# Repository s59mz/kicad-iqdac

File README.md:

# iqdac
AD9957 DAC test module for the Z-Turn I/O expansion card

Schematic:
[iqdac.pdf](iqdac.pdf)

BOM:
[iqdac.csv](iqdac.csv)

Gerbers:
[gerbers.zip](https://github.com/s59mz/kicad-iqdac/raw/main/gerbers.zip)

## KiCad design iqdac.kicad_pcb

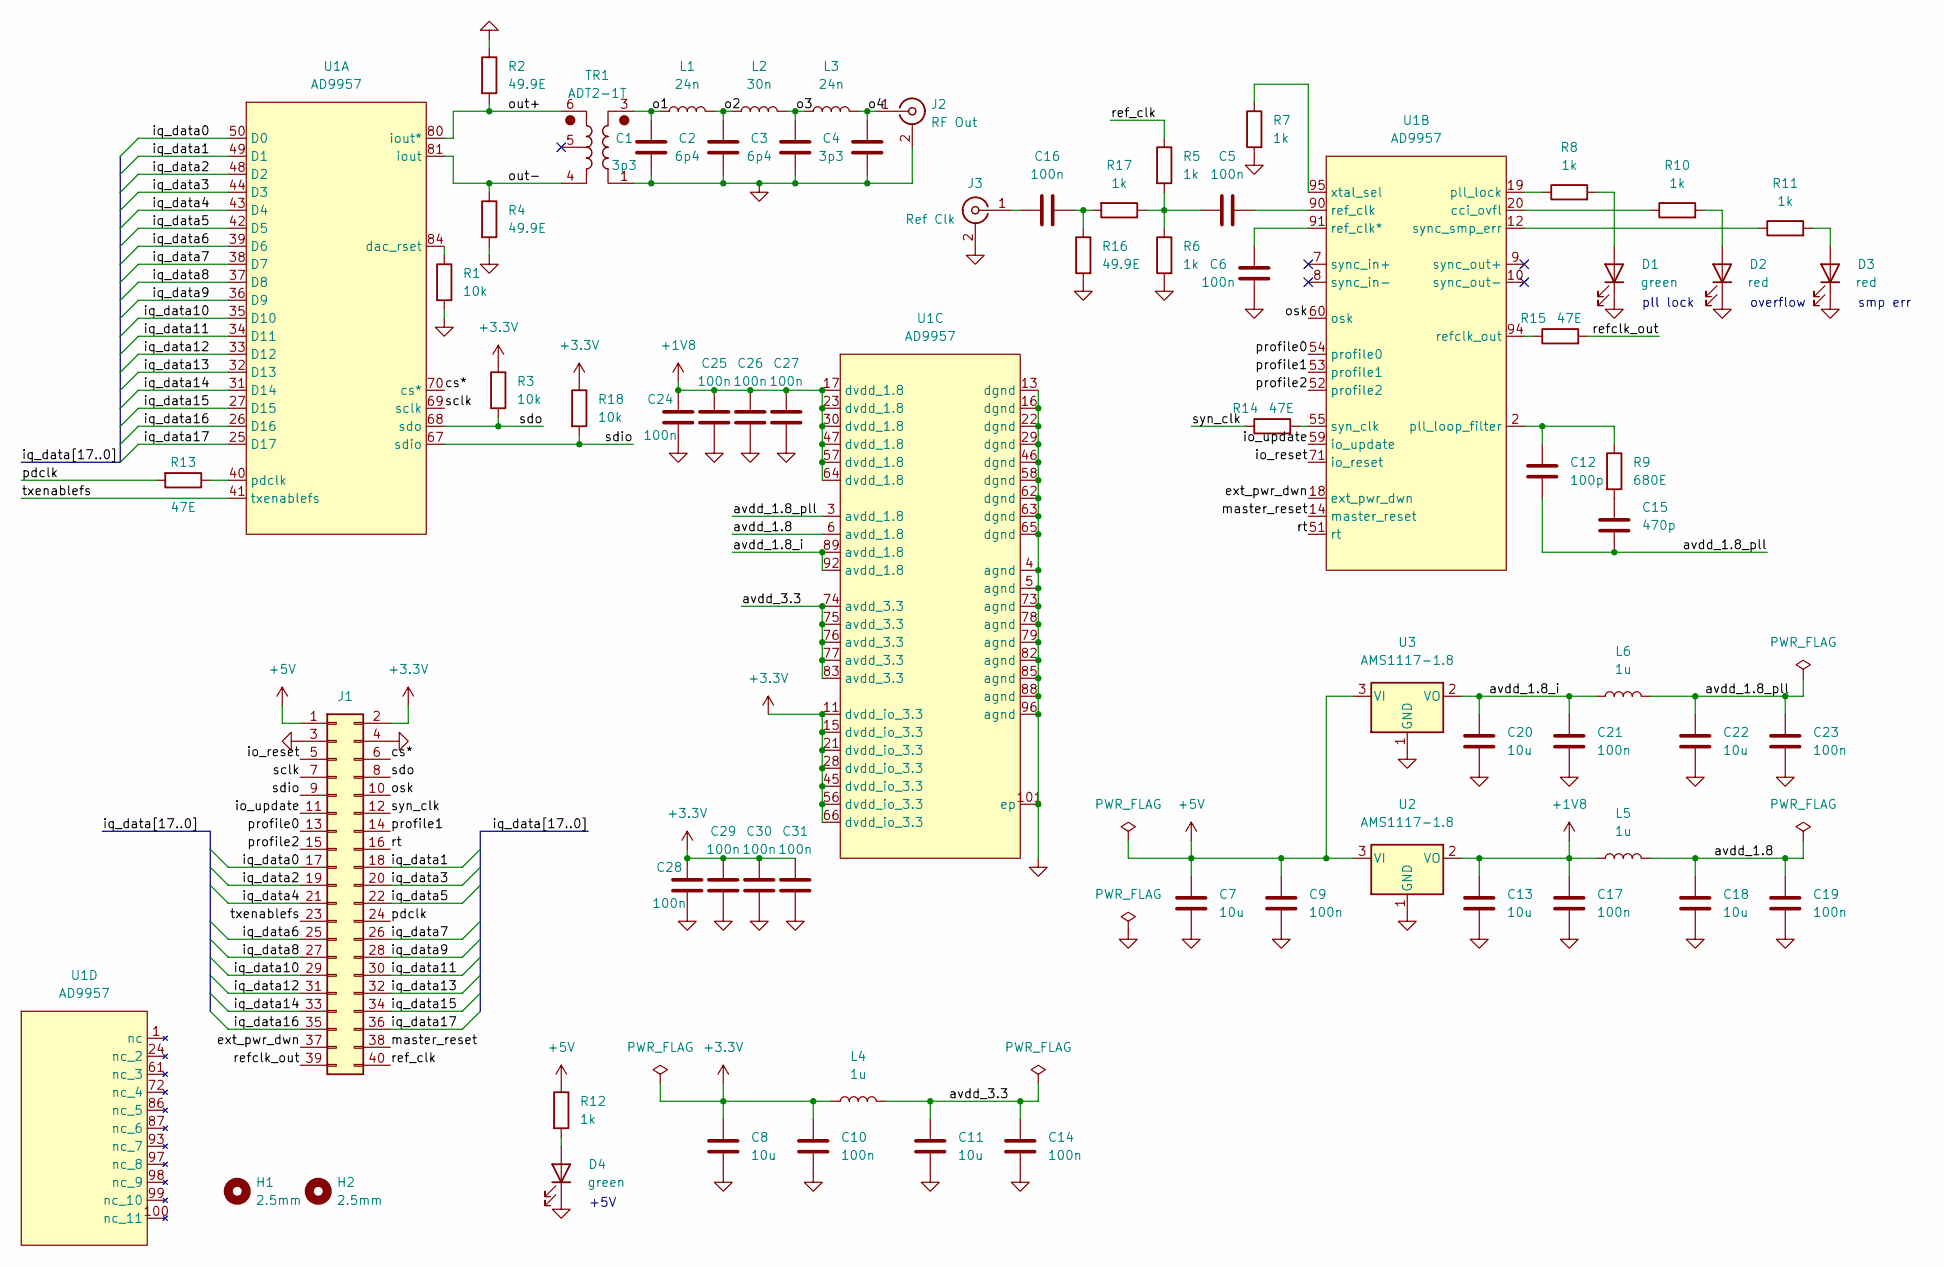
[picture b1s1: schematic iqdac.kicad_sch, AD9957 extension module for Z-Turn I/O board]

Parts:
C1, C4: 3p3; C_0603_1608Metric_Pad1.08x0.95mm_HandSolder
C2, C3: 6p4; C_0603_1608Metric_Pad1.08x0.95mm_HandSolder
C5, C6, C9, C10, C14, C16, C17, C19, C21, C23, C24, C25, C26, C27, C28, C29, C30, C31: 100n; C_0603_1608Metric_Pad1.08x0.95mm_HandSolder
C7, C8, C11, C13, C18, C20, C22: 10u; C_0603_1608Metric_Pad1.08x0.95mm_HandSolder
C12: 100p; C_0603_1608Metric_Pad1.08x0.95mm_HandSolder
C15: 470p; C_0603_1608Metric_Pad1.08x0.95mm_HandSolder
D1, D4: green; LED_0603_1608Metric_Pad1.05x0.95mm_HandSolder
D2, D3: red; LED_0603_1608Metric_Pad1.05x0.95mm_HandSolder
H1, H2: 2.5mm; MountingHole_2.5mm
J1: Conn_02x20_Odd_Even; PinSocket_2x20_P2.54mm_Vertical
J2: RF Out; SMA_Amphenol_132291_Vertical
J3: Ref Clk; SMA_Amphenol_132291_Vertical
L1, L3: 24n; L_0603_1608Metric_Pad1.05x0.95mm_HandSolder
L2: 30n; L_0603_1608Metric_Pad1.05x0.95mm_HandSolder
L4, L5, L6: 1u; L_1206_3216Metric_Pad1.22x1.90mm_HandSolder
R1, R3, R18: 10k; R_0603_1608Metric_Pad0.98x0.95mm_HandSolder
R2, R4, R16: 49.9E; R_0603_1608Metric_Pad0.98x0.95mm_HandSolder
R5, R6, R7, R8, R10, R11, R12, R17: 1k; R_0603_1608Metric_Pad0.98x0.95mm_HandSolder
R9: 680E; R_0603_1608Metric_Pad0.98x0.95mm_HandSolder
R13, R14, R15: 47E; R_0603_1608Metric_Pad0.98x0.95mm_HandSolder
TR1: ADT2-1T; Mini-Circuits_CD542_H2.84mm
U1: AD9957; TQFP-100-1EP_14x14mm_P0.5mm_EP5x5mm
U2: AMS1117-1.8; TO-252-2
U3: AMS1117-1.8; SOT-223-3_TabPin2

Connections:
+1V8: C13.1, C17.1, C24.2, C25.2, C26.2, C27.2, L5.1, U1.17 (dvdd_1.8), U1.23 (dvdd_1.8), U1.30 (dvdd_1.8), U1.47 (dvdd_1.8), U1.57 (dvdd_1.8), U1.64 (dvdd_1.8), U2.2 (VO)
+3.3V: C8.1, C10.1, C28.2, C29.2, C30.2, C31.2, J1.2, L4.1, R3.1, R18.1, U1.11 (dvdd_io_3.3), U1.15 (dvdd_io_3.3), U1.21 (dvdd_io_3.3), U1.28 (dvdd_io_3.3), U1.45 (dvdd_io_3.3), U1.56 (dvdd_io_3.3), U1.66 (dvdd_io_3.3)
+5V: C7.1, C9.1, J1.1, R12.1, U2.3 (VI), U3.3 (VI)
/avdd_1.8: C18.1, C19.1, L5.2, U1.6 (avdd_1.8)
/avdd_1.8_i: C20.1, C21.1, L6.1, U1.89 (avdd_1.8), U1.92 (avdd_1.8), U3.2 (VO)
/avdd_1.8_pll: C12.2, C15.2, C22.1, C23.1, L6.2, U1.3 (avdd_1.8)
/avdd_3.3: C11.1, C14.1, L4.2, U1.74 (avdd_3.3), U1.75 (avdd_3.3), U1.76 (avdd_3.3), U1.77 (avdd_3.3), U1.83 (avdd_3.3)
/cs*: J1.6, U1.70 (cs*)
/ext_pwr_dwn: J1.37, U1.18 (ext_pwr_dwn)
/io_reset: J1.5, U1.71 (io_reset)
/io_update: J1.11, U1.59 (io_update)
/iq_data0: J1.17, U1.50 (D0)
/iq_data1: J1.18, U1.49 (D1)
/iq_data2: J1.19, U1.48 (D2)
/iq_data3: J1.20, U1.44 (D3)
/iq_data4: J1.21, U1.43 (D4)
/iq_data5: J1.22, U1.42 (D5)
/iq_data6: J1.25, U1.39 (D6)
/iq_data7: J1.26, U1.38 (D7)
/iq_data8: J1.27, U1.37 (D8)
/iq_data9: J1.28, U1.36 (D9)
/iq_data10: J1.29, U1.35 (D10)
/iq_data11: J1.30, U1.34 (D11)
/iq_data12: J1.31, U1.33 (D12)
/iq_data13: J1.32, U1.32 (D13)
/iq_data14: J1.33, U1.31 (D14)
/iq_data15: J1.34, U1.27 (D15)
/iq_data16: J1.35, U1.26 (D16)
/iq_data17: J1.36, U1.25 (D17)
/master_reset: J1.38, U1.14 (master_reset)
/o1: C1.2, L1.1, TR1.3
/o2: C2.2, L1.2, L2.1
/o3: C3.2, L2.2, L3.1
/o4: C4.2, J2.1 (In), L3.2
/osk: J1.10, U1.60 (osk)
/out+: R2.2, TR1.6, U1.80 (iout*)
/out-: R4.1, TR1.4, U1.81 (iout)
/pdclk: J1.24, R13.2
/profile0: J1.13, U1.54 (profile0)
/profile1: J1.14, U1.53 (profile1)
/profile2: J1.15, U1.52 (profile2)
/ref_clk: J1.40, R5.1
/refclk_out: J1.39, R15.2
/rt: J1.16, U1.51 (rt)
/sclk: J1.7, U1.69 (sclk)
/sdio: J1.9, R18.2, U1.67 (sdio)
/sdo: J1.8, R3.2, U1.68 (sdo)
/syn_clk: J1.12, R14.1
/txenablefs: J1.23, U1.41 (txenablefs)
GND: C1.1, C2.1, C3.1, C4.1, C6.1, C7.2, C8.2, C9.2, C10.2, C11.2, C13.2, C14.2, C17.2, C18.2, C19.2, C20.2, C21.2, C22.2, C23.2, C24.1, C25.1, C26.1, C27.1, C28.1, C29.1, C30.1, C31.1, D1.1 (K), D2.1 (K), D3.1 (K), D4.1 (K), J1.3, J1.4, J2.2 (Ext), J3.2 (Ext), R1.2, R2.1, R4.2, R6.2, R7.2, R16.2, TR1.1, U1.4 (agnd), U1.5 (agnd), U1.13 (dgnd), U1.16 (dgnd), U1.22 (dgnd), U1.29 (dgnd), U1.46 (dgnd), U1.58 (dgnd), U1.62 (dgnd), U1.63 (dgnd), U1.65 (dgnd), U1.73 (agnd), U1.78 (agnd), U1.79 (agnd), U1.82 (agnd), U1.85 (agnd), U1.88 (agnd), U1.96 (agnd), U1.101 (ep), U2.1 (GND), U3.1 (GND)
unnamed: C5.1, R5.2, R6.1, R17.1
unnamed: C5.2, U1.90 (ref_clk)
unnamed: C6.2, U1.91 (ref_clk*)
unnamed: C12.1, R9.1, U1.2 (pll_loop_filter)
unnamed: C15.1, R9.2
unnamed: C16.1, J3.1 (In)
unnamed: C16.2, R16.1, R17.2
unnamed: D1.2 (A), R8.2
unnamed: D2.2 (A), R10.2
unnamed: D3.2 (A), R11.2
unnamed: D4.2 (A), R12.2
unnamed: R1.1, U1.84 (dac_rset)
unnamed: R7.1, U1.95 (xtal_sel)
unnamed: R8.1, U1.19 (pll_lock)
unnamed: R10.1, U1.20 (cci_ovfl)
unnamed: R11.1, U1.12 (sync_smp_err)
unnamed: R13.1, U1.40 (pdclk)
unnamed: R14.2, U1.55 (syn_clk)
unnamed: R15.1, U1.94 (refclk_out)

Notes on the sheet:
+5V
smp err
pll lock
overflow

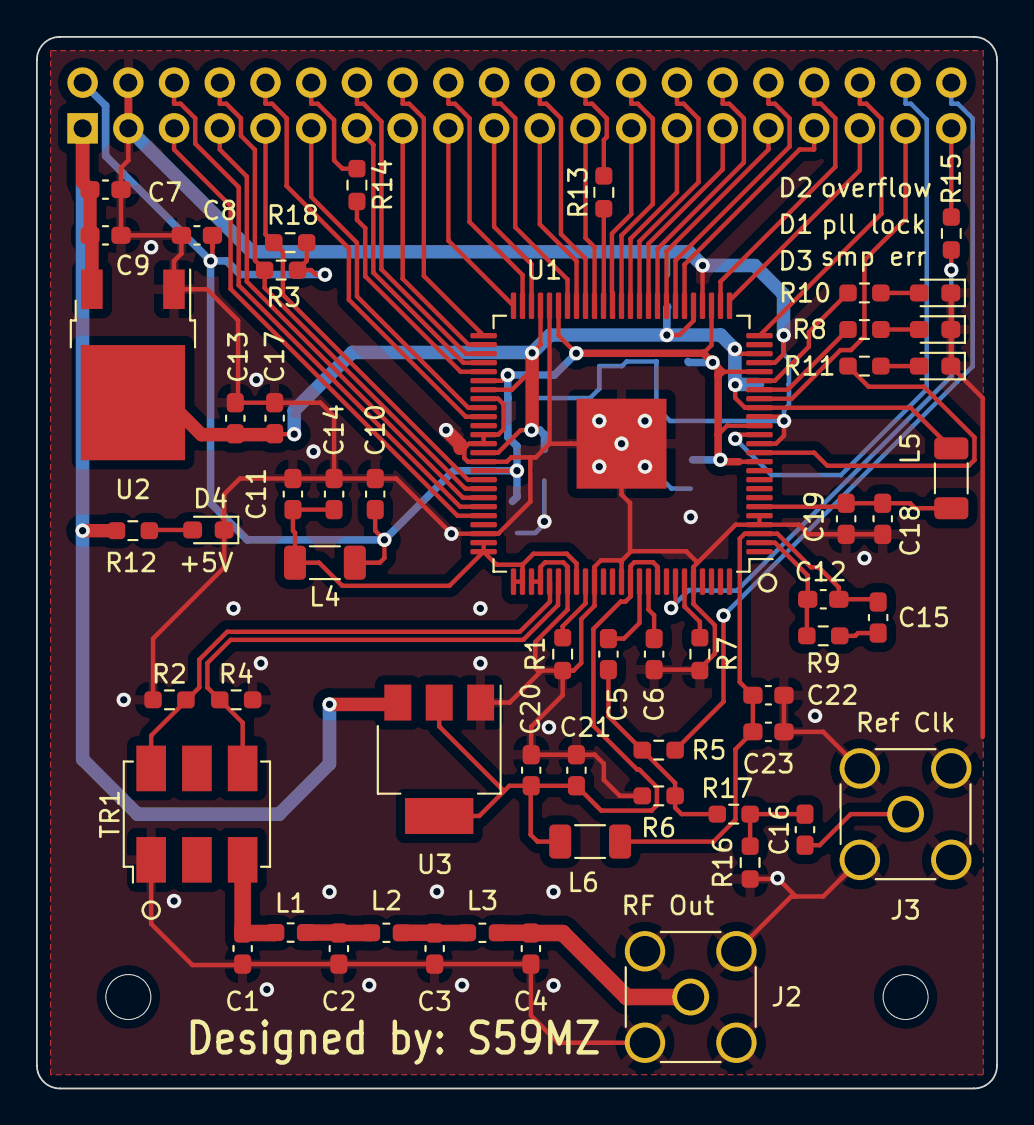
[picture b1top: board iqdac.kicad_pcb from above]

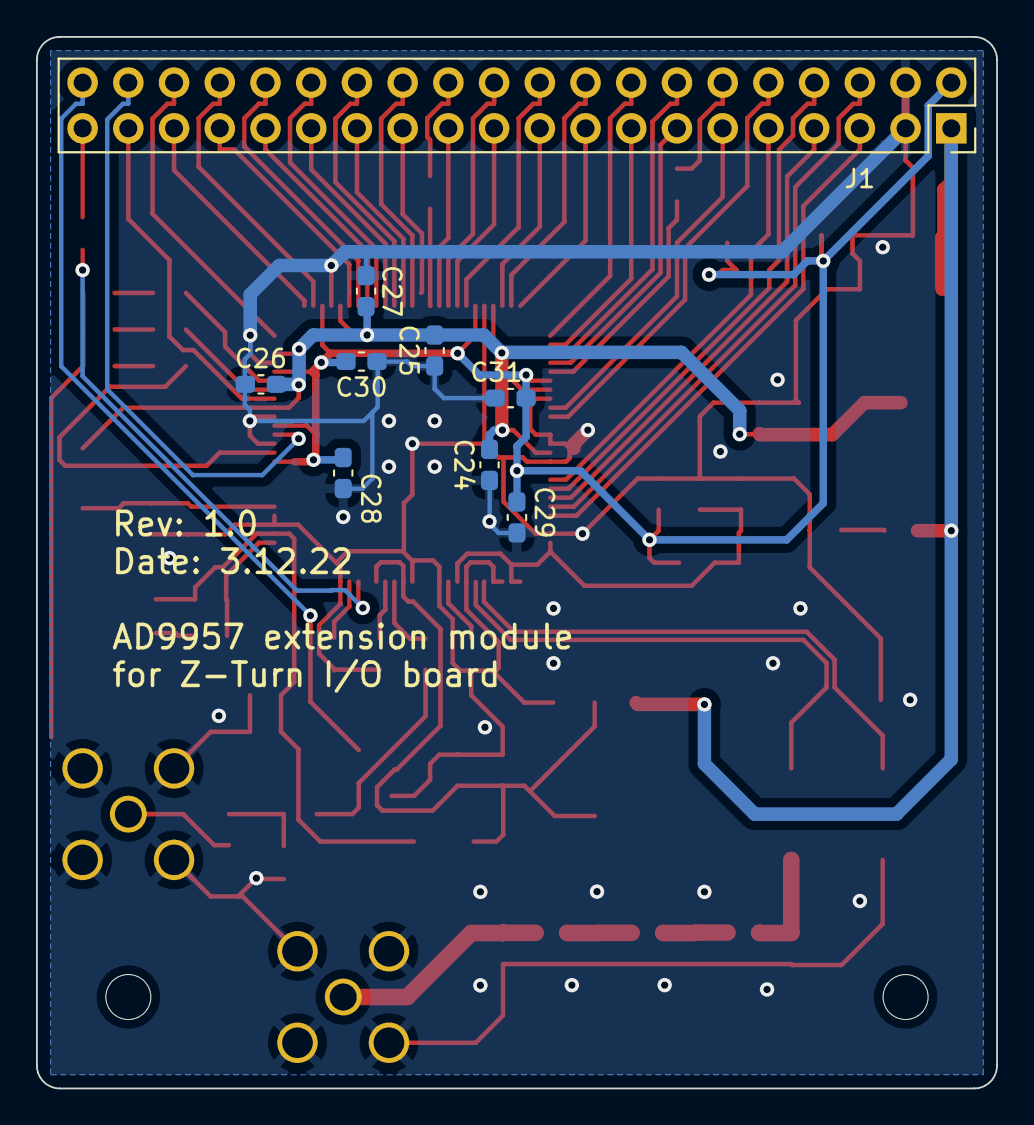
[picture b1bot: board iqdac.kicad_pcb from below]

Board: 2 copper layers, 53.3 x 58.4 mm, 68 parts (9 on the bottom side), 69 nets.

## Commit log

2024-08-11 add screenshots
